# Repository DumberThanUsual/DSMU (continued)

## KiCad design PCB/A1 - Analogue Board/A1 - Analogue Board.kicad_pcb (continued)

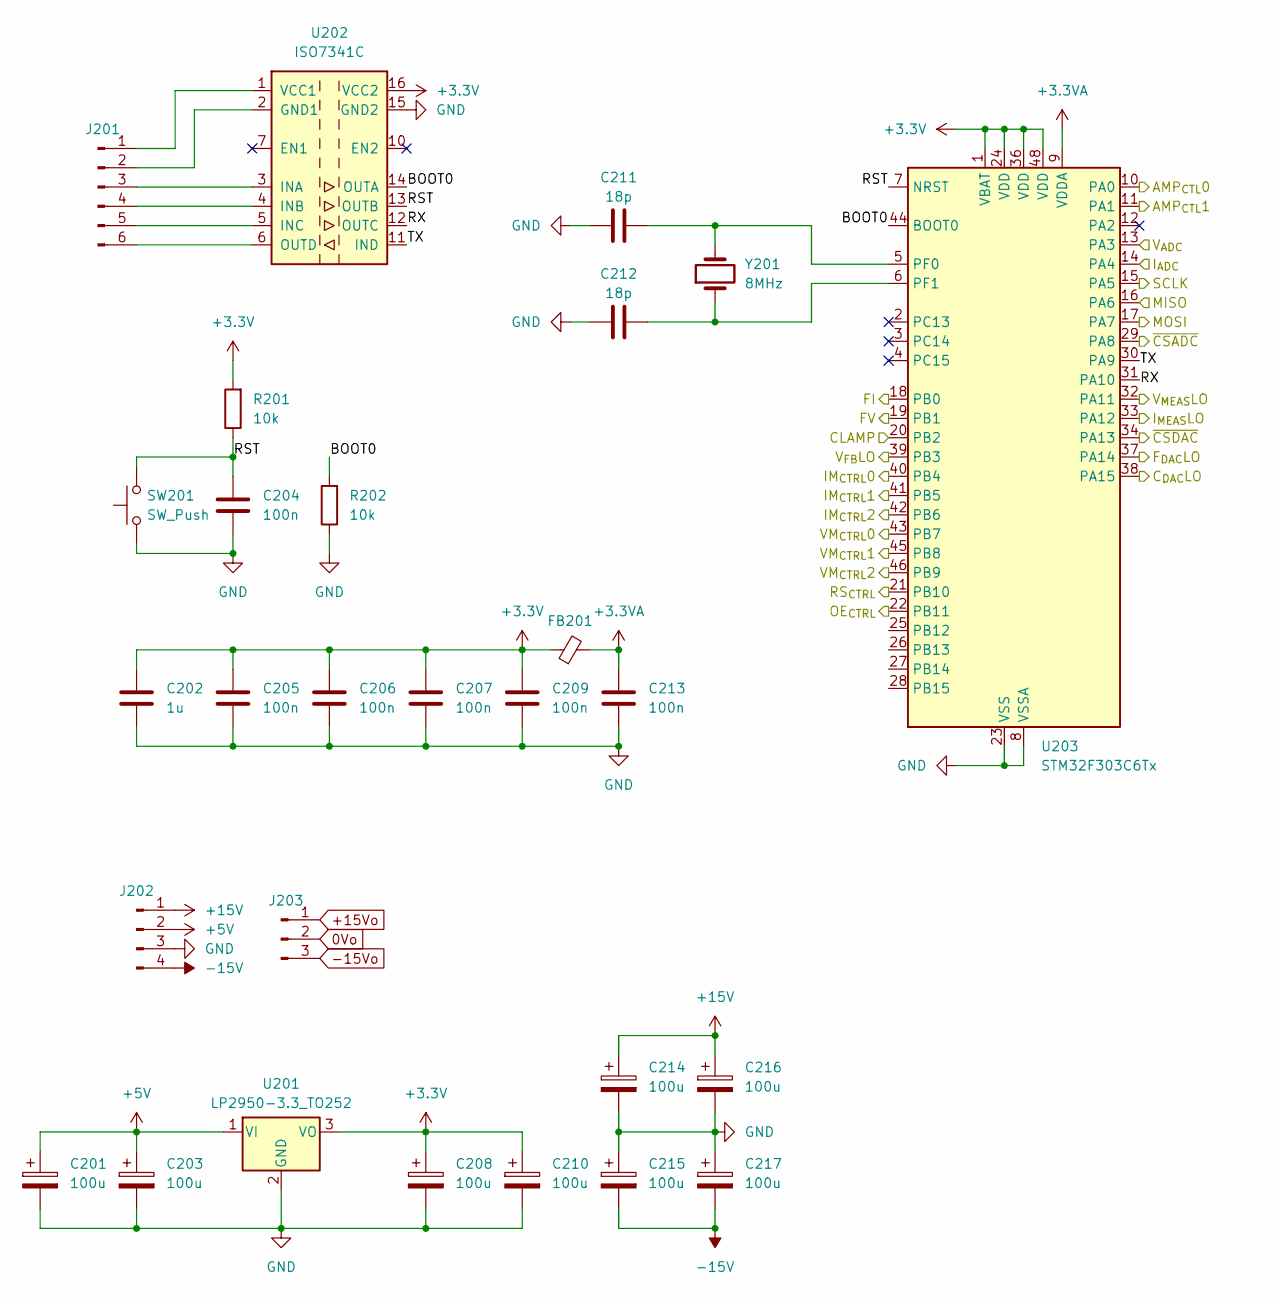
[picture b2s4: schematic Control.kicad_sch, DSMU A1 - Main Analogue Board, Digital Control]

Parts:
C201, C203, C208, C210, C214, C215, C216, C217: 100u; CP_Radial_D8.0mm_P3.50mm
C202: 1u; C_0603_1608Metric
C204, C205, C206, C207, C209, C213: 100n; C_0603_1608Metric
C211, C212: 18p; C_0603_1608Metric
FB201: FerriteBead_Small; L_0603_1608Metric
J201: Conn_01x06_Pin; PinHeader_1x06_P2.54mm_Vertical
J202: Conn_01x04_Pin; PinHeader_1x04_P2.54mm_Vertical
J203: Conn_01x03_Pin; PinHeader_1x03_P2.54mm_Vertical
R201, R202: 10k; R_0603_1608Metric
SW201: SW_Push; SW_SPST_Omron_B3FS-105xP
U201: LP2950-3.3_TO252; TO-252-3_TabPin2
U202: ISO7341C; SOIC-16W_7.5x10.3mm_P1.27mm
U203: STM32F303C6Tx; LQFP-48_7x7mm_P0.5mm
Y201: 8MHz; Crystal_HC18-U_Vertical

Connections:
0Vo: J203.2; also elsewhere on the board
+3.3V: C202.1, C205.1, C206.1, C207.1, C208.1, C209.1, C210.1, FB201.1, R201.2, U201.3 (VO), U202.16 (VCC2), U203.1 (VBAT), U203.24 (VDD), U203.36 (VDD), U203.48 (VDD); also elsewhere on the board
+3.3VA: C213.1, FB201.2, U203.9 (VDDA)
+5V: C201.1, C203.1, J202.2, U201.1 (VI); also elsewhere on the board
+15V: C214.1, C216.1, J202.1; also elsewhere on the board
+15Vo: J203.1; also elsewhere on the board
-15V: C215.2, C217.2, J202.4; also elsewhere on the board
-15Vo: J203.3; also elsewhere on the board
/Clamp: U203.20 (PB2); also elsewhere on the board
/Data Converters/C_{DAC}LO: U203.38 (PA15); also elsewhere on the board
/Data Converters/F_{DAC}LO: U203.37 (PA14); also elsewhere on the board
/Data Converters/I_{MEAS}LO: U203.33 (PA12); also elsewhere on the board
/Data Converters/MISO: U203.16 (PA6); also elsewhere on the board
/Data Converters/MOSI: U203.17 (PA7); also elsewhere on the board
/Data Converters/SCLK: U203.15 (PA5); also elsewhere on the board
/Data Converters/V_{MEAS}LO: U203.32 (PA11); also elsewhere on the board
/Data Converters/~CSADC: U203.29 (PA8); also elsewhere on the board
/Data Converters/~CSDAC: U203.34 (PA13); also elsewhere on the board
/Digital Control/AMP_{CTL}0: U203.10 (PA0); also elsewhere on the board
/Digital Control/AMP_{CTL}1: U203.11 (PA1); also elsewhere on the board
/Digital Control/BOOT0: R202.2, U202.14 (OUTA), U203.44 (BOOT0)
/Digital Control/I_{ADC}: U203.14 (PA4); also elsewhere on the board
/Digital Control/RST: C204.1, R201.1, SW201.2, U202.13 (OUTB), U203.7 (NRST)
/Digital Control/RX: U202.12 (OUTC), U203.31 (PA10)
/Digital Control/TX: U202.11 (IND), U203.30 (PA9)
/Digital Control/V_{ADC}: U203.13 (PA3); also elsewhere on the board
/FI: U203.18 (PB0); also elsewhere on the board
/FV: U203.19 (PB1); also elsewhere on the board
/IM_{CTRL}0: U203.40 (PB4); also elsewhere on the board
/IM_{CTRL}1: U203.41 (PB5); also elsewhere on the board
/IM_{CTRL}2: U203.42 (PB6); also elsewhere on the board
/OE_{CTRL}: U203.22 (PB11); also elsewhere on the board
/RS_{CTRL}: U203.21 (PB10); also elsewhere on the board
/VM_{CTRL}0: U203.43 (PB7); also elsewhere on the board
/VM_{CTRL}1: U203.45 (PB8); also elsewhere on the board
/VM_{CTRL}2: U203.46 (PB9); also elsewhere on the board
/V_{FB}LO: U203.39 (PB3); also elsewhere on the board
GND: C201.2, C202.2, C203.2, C204.2, C205.2, C206.2, C207.2, C208.2, C209.2, C210.2, C211.1, C212.1, C213.2, C214.2, C215.1, C216.2, C217.1, J202.3, R202.1, SW201.1, U201.2 (GND), U202.9 (GND2), U202.15 (GND2), U203.8 (VSSA), U203.23 (VSS), U203.35 (VSS), U203.47 (VSS); also elsewhere on the board
unnamed: J201.1, U202.1 (VCC1)
unnamed: J201.2, U202.2 (GND1), U202.8 (GND1)
unnamed: J201.3, U202.3 (INA)
unnamed: J201.4, U202.4 (INB)
unnamed: J201.5, U202.5 (INC)
unnamed: J201.6, U202.6 (OUTD)
unnamed: C211.2, U203.5 (PF0), Y201.2
unnamed: C212.2, U203.6 (PF1), Y201.1

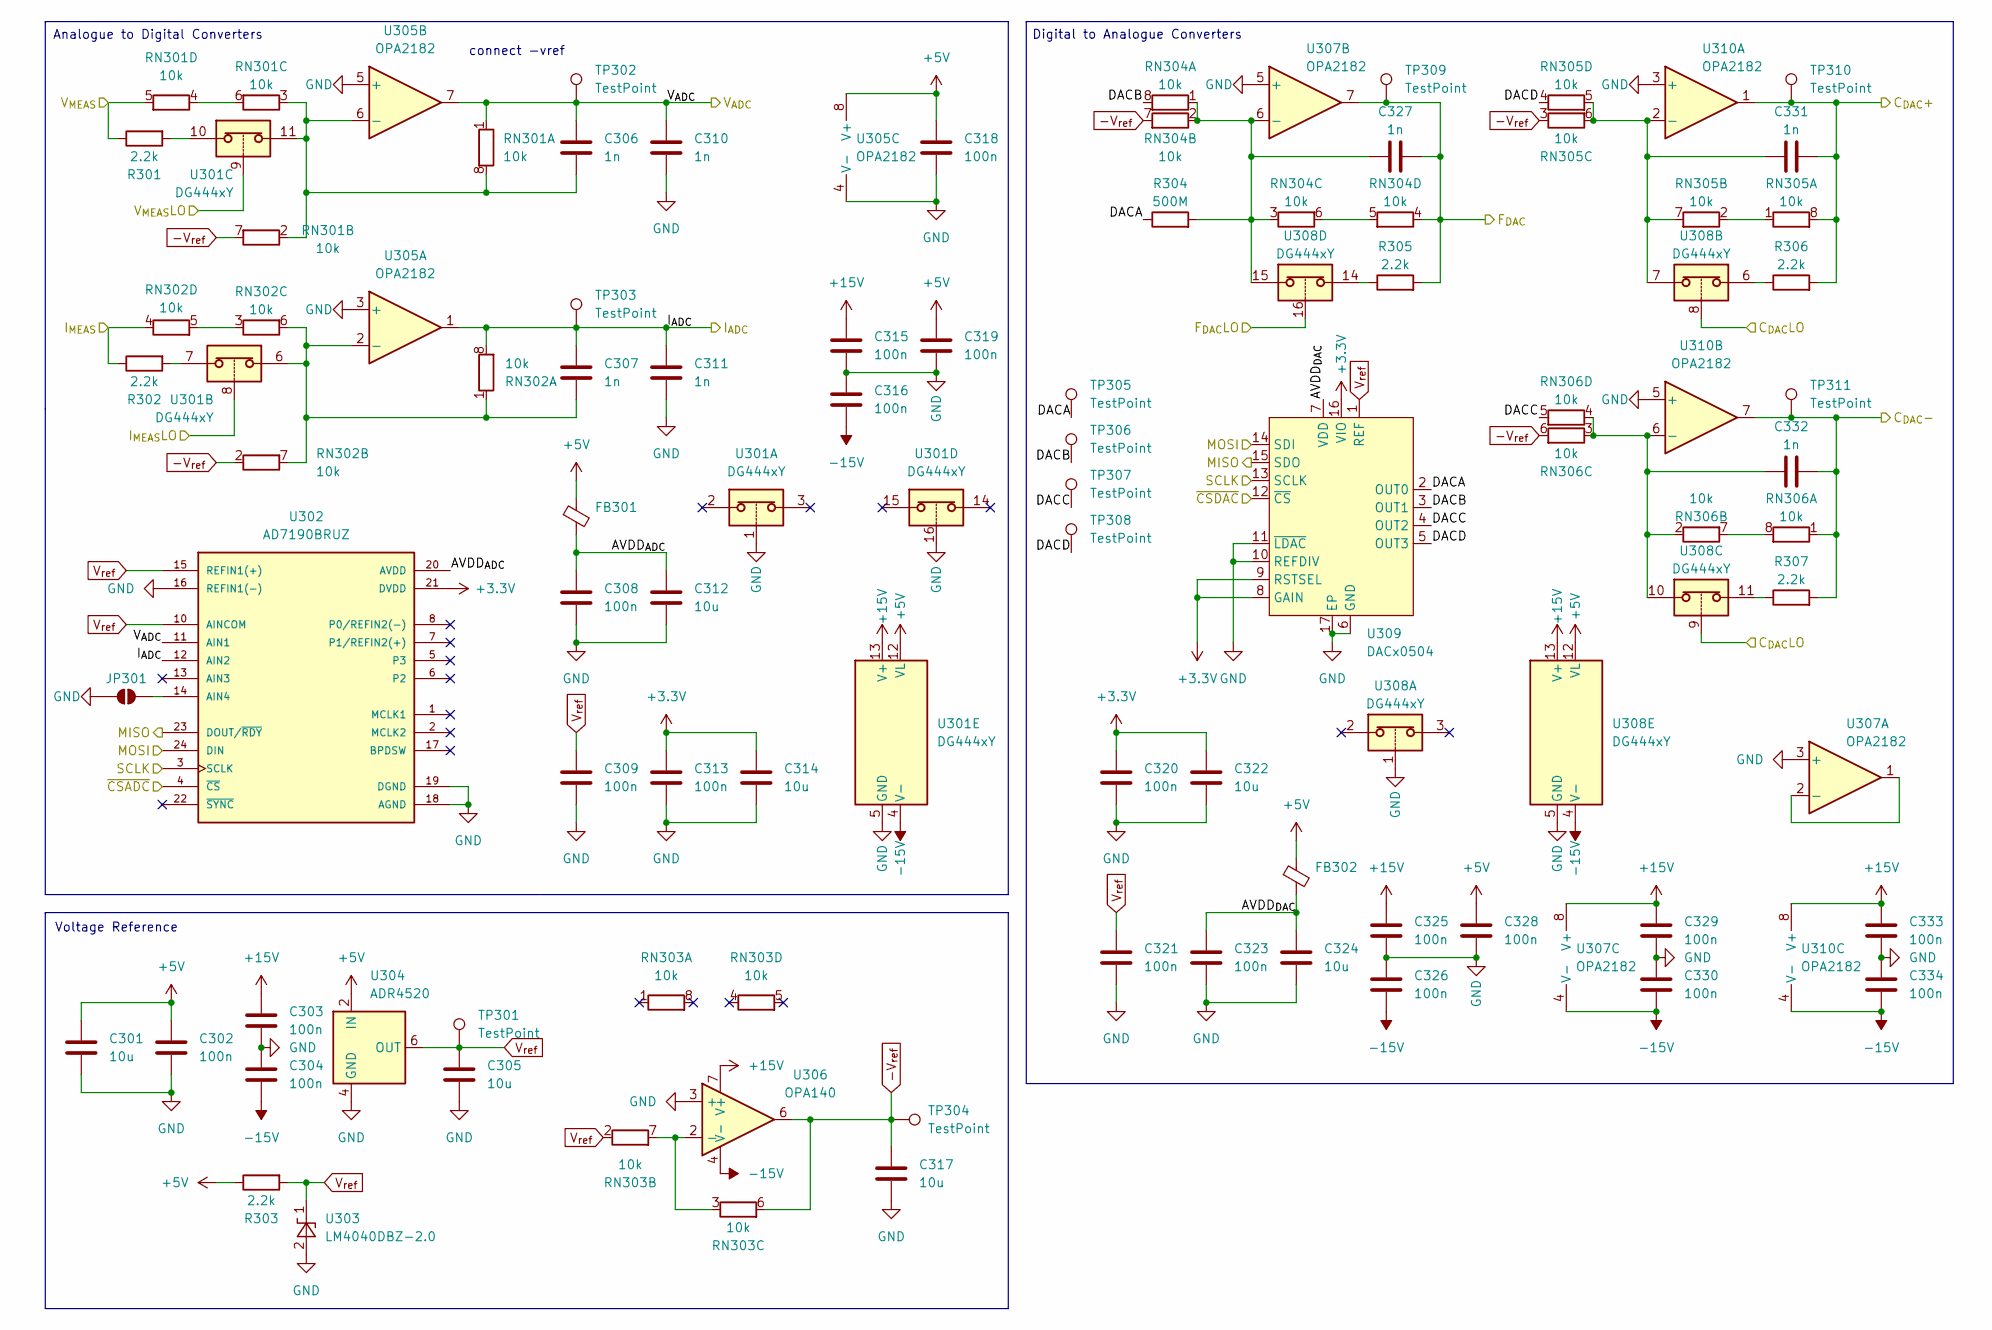
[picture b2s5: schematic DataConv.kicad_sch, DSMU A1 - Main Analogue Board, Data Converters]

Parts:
C301, C305, C312, C314, C317, C322, C324: 10u; C_0805_2012Metric
C302, C303, C304, C308, C309, C313, C315, C316, C318, C319, C320, C321, C323, C325, C326, C328, C329, C330, C333, C334: 100n; C_0603_1608Metric
C306, C307, C310, C311, C327, C331, C332: 1n; C_0603_1608Metric
FB301, FB302: FerriteBead_Small; L_0603_1608Metric
JP301: SolderJumper_2_Open; SolderJumper-2_P1.3mm_Open_RoundedPad1.0x1.5mm
R301, R302, R303, R305, R306, R307: 2.2k; R_0603_1608Metric
R304: 500M; R_1206_3216Metric
RN301, RN302, RN303, RN304, RN305, RN306: 10k; R_Array_Concave_4x0603
TP301, TP302, TP303, TP304, TP305, TP306, TP307, TP308, TP309, TP310, TP311: TestPoint; Pin_D1.0mm_L10.0mm
U301, U308: DG444xY; SOIC-16_3.9x9.9mm_P1.27mm
U302: AD7190BRUZ; SOP65P640X120-24N
U303: LM4040DBZ-2.0; SOT-23
U304: ADR4520; SOIC-8_3.9x4.9mm_P1.27mm
U305, U307, U310: OPA2182; SOIC-8_3.9x4.9mm_P1.27mm
U306: OPA140; SOIC-8_3.9x4.9mm_P1.27mm
U309: DACx0504; WQFN-16-1EP_3x3mm_P0.5mm_EP1.68x1.68mm_ThermalVias

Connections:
+3.3V: C313.1, C314.1, C320.1, C322.1, U302.21 (DVDD), U309.8 (GAIN), U309.9 (RSTSEL), U309.16 (VIO); also elsewhere on the board
+5V: C301.1, C302.1, C318.1, C319.1, C328.1, FB301.1, FB302.1, R303.1, U301.12 (VL), U304.2 (IN), U305.8 (V+), U308.12 (VL); also elsewhere on the board
+15V: C303.1, C315.1, C325.1, C329.1, C333.1, U301.13 (V+), U306.7 (V+), U307.8 (V+), U308.13 (V+), U310.8 (V+); also elsewhere on the board
-15V: C304.2, C316.2, C326.2, C330.2, C334.2, U301.4 (V-), U306.4 (V-), U307.4 (V-), U308.4 (V-), U310.4 (V-); also elsewhere on the board
-V_{ref}: C317.1, RN301.7 (R2.2), RN302.2 (R2.1), RN303.6 (R3.2), RN304.7 (R2.2), RN305.3 (R3.1), RN306.6 (R3.2), TP304.1, U306.6
/Crossover and Amplifier Control/C_{DAC}+: C331.2, R306.2, RN305.8 (R1.2), TP310.1, U310.1; also elsewhere on the board
/Crossover and Amplifier Control/C_{DAC}-: C332.2, R307.2, RN306.1 (R1.1), TP311.1, U310.7; also elsewhere on the board
/Crossover and Amplifier Control/F_{DAC}: C327.2, R305.2, RN304.4 (R4.1), TP309.1, U307.7; also elsewhere on the board
/Data Converters/AVDD_{ADC}: C308.1, C312.1, FB301.2, U302.20 (AVDD)
/Data Converters/AVDD_{DAC}: C323.1, C324.1, FB302.2, U309.7 (VDD)
/Data Converters/C_{DAC}LO: U308.8, U308.9; also elsewhere on the board
/Data Converters/DACA: R304.1, TP305.1, U309.2 (OUT0)
/Data Converters/DACB: RN304.8 (R1.2), TP306.1, U309.3 (OUT1)
/Data Converters/DACC: RN306.5 (R4.2), TP307.1, U309.4 (OUT2)
/Data Converters/DACD: RN305.4 (R4.1), TP308.1, U309.5 (OUT3)
/Data Converters/F_{DAC}LO: U308.16; also elsewhere on the board
/Data Converters/I_{ADC}: C307.1, C311.1, RN302.8 (R1.2), TP303.1, U302.12 (AIN2), U305.1; also elsewhere on the board
/Data Converters/I_{MEAS}LO: U301.8; also elsewhere on the board
/Data Converters/MISO: U302.23 (DOUT/~RDY), U309.15 (SDO); also elsewhere on the board
/Data Converters/MOSI: U302.24 (DIN), U309.14 (SDI); also elsewhere on the board
/Data Converters/SCLK: U302.3 (SCLK), U309.13 (SCLK); also elsewhere on the board
/Data Converters/V_{ADC}: C306.1, C310.1, RN301.1 (R1.1), TP302.1, U302.11 (AIN1), U305.7; also elsewhere on the board
/Data Converters/V_{MEAS}LO: U301.9; also elsewhere on the board
/Data Converters/~CSADC: U302.4 (~CS); also elsewhere on the board
/Data Converters/~CSDAC: U309.12 (~CS); also elsewhere on the board
/IM: R302.1, RN302.4 (R4.1); also elsewhere on the board
/VM: R301.1, RN301.5 (R4.2); also elsewhere on the board
GND: C301.2, C302.2, C303.2, C304.1, C305.2, C308.2, C309.2, C310.2, C311.2, C312.2, C313.2, C314.2, C315.2, C316.1, C317.2, C318.2, C319.2, C320.2, C321.2, C322.2, C323.2, C324.2, C325.2, C326.1, C328.2, C329.2, C330.1, C333.2, C334.1, JP301.2 (B), U301.1, U301.5 (GND), U301.16, U302.16 (REFIN1(-)), U302.18 (AGND), U302.19 (DGND), U303.2 (A), U304.4 (GND), U305.3 (+), U305.4 (V-), U305.5 (+), U306.3 (+), U307.3 (+), U307.5 (+), U308.1, U308.5 (GND), U309.6 (GND), U309.10 (REFDIV), U309.11 (~LDAC), U309.17 (EP), U310.3 (+), U310.5 (+); also elsewhere on the board
unnamed: JP301.1 (A), U302.14 (AIN4)
unnamed: R301.2, U301.10
unnamed: R302.2, U301.7
unnamed: R305.1, U308.14
unnamed: R306.1, U308.6
unnamed: R307.1, U308.11
unnamed: C306.2, RN301.2 (R2.1), RN301.3 (R3.1), RN301.8 (R1.2), U301.11, U305.6 (-)
unnamed: RN301.4 (R4.1), RN301.6 (R3.2)
unnamed: C307.2, RN302.1 (R1.1), RN302.6 (R3.2), RN302.7 (R2.2), U301.6, U305.2 (-)
unnamed: RN302.3 (R3.1), RN302.5 (R4.2)
unnamed: RN303.3 (R3.1), RN303.7 (R2.2), U306.2 (-)
unnamed: C327.1, R304.2, RN304.1 (R1.1), RN304.2 (R2.1), RN304.3 (R3.1), U307.6 (-), U308.15
unnamed: RN304.5 (R4.2), RN304.6 (R3.2)
unnamed: RN305.1 (R1.1), RN305.2 (R2.1)
unnamed: C331.1, RN305.5 (R4.2), RN305.6 (R3.2), RN305.7 (R2.2), U308.7, U310.2 (-)
unnamed: RN306.7 (R2.2), RN306.8 (R1.2)
unnamed: C332.1, RN306.2 (R2.1), RN306.3 (R3.1), RN306.4 (R4.1), U308.10, U310.6 (-)
unnamed: U307.1, U307.2 (-)
V_{ref}: C305.1, C309.1, C321.1, R303.2, RN303.2 (R2.1), TP301.1, U302.10 (AINCOM), U302.15 (REFIN1(+)), U303.1 (K), U304.6 (OUT), U309.1 (REF)

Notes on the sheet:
connect -vref
Voltage Reference
Digital to Analogue Converters
Analogue to Digital Converters

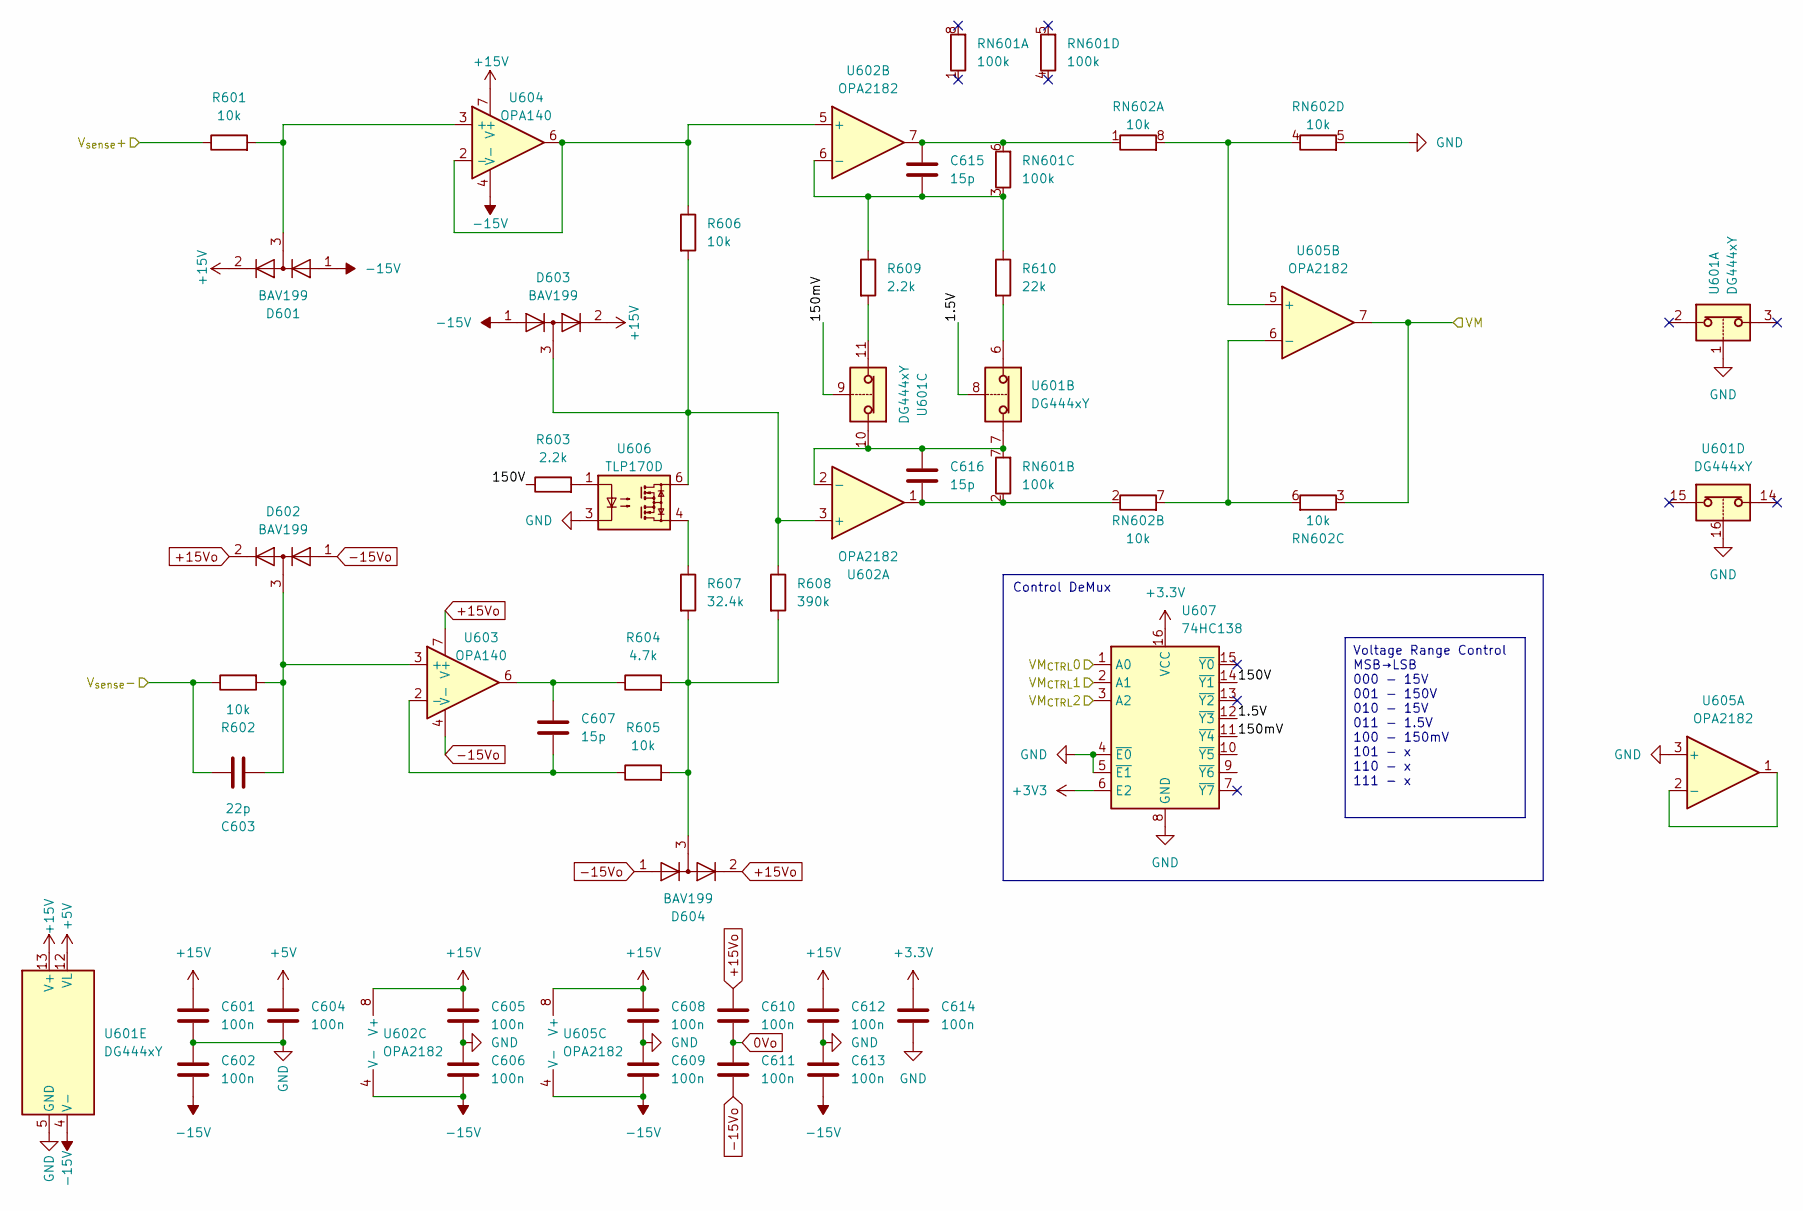
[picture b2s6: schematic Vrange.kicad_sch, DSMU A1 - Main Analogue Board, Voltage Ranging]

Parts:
C601, C602, C604, C605, C606, C608, C609, C610, C611, C612, C613, C614: 100n; C_0603_1608Metric
C603: 22p; C_0603_1608Metric
C607, C615, C616: 15p; C_0603_1608Metric
D601, D602, D603, D604: BAV199; SOT-23
R601, R602, R605, R606: 10k; R_0603_1608Metric
R603, R609: 2.2k; R_0603_1608Metric
R604: 4.7k; R_0603_1608Metric
R607: 32.4k; R_0805_2012Metric
R608: 390k; R_1206_3216Metric
R610: 22k; R_0603_1608Metric
RN601: 100k; R_Array_Concave_4x0603
RN602: 10k; R_Array_Concave_4x0603
U601: DG444xY; SOIC-16_3.9x9.9mm_P1.27mm
U602, U605: OPA2182; SOIC-8_3.9x4.9mm_P1.27mm
U603, U604: OPA140; SOIC-8_3.9x4.9mm_P1.27mm
U606: TLP170D; MFSOP6-4_4.4x3.6mm_P1.27mm
U607: 74HC138; SOIC-16_3.9x9.9mm_P1.27mm

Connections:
0Vo: C610.2, C611.1; also elsewhere on the board
+3.3V: C614.1, U607.16 (VCC); also elsewhere on the board
+3V3: U607.6 (E2); also elsewhere on the board
+5V: C604.1, U601.12 (VL); also elsewhere on the board
+15V: C601.1, C605.1, C608.1, C612.1, D601.2 (A), D603.2 (A), U601.13 (V+), U602.8 (V+), U604.7 (V+), U605.8 (V+); also elsewhere on the board
+15Vo: C610.1, D602.2 (A), D604.2 (A), U603.7 (V+); also elsewhere on the board
-15V: C602.2, C606.2, C609.2, C613.2, D601.1 (K), D603.1 (K), U601.4 (V-), U602.4 (V-), U604.4 (V-), U605.4 (V-); also elsewhere on the board
-15Vo: C611.2, D602.1 (K), D604.1 (K), U603.4 (V-); also elsewhere on the board
/VM: RN602.3 (R3.1), U605.7; also elsewhere on the board
/VM_{CTRL}0: U607.1 (A0); also elsewhere on the board
/VM_{CTRL}1: U607.2 (A1); also elsewhere on the board
/VM_{CTRL}2: U607.3 (A2); also elsewhere on the board
/Voltage Ranging/1.5V: U601.8, U607.12 (~Y3)
/Voltage Ranging/150V: R603.1, U607.14 (~Y1)
/Voltage Ranging/150mV: U601.9, U607.11 (~Y4)
/Voltage Ranging/V_{sense}+: R601.1; also elsewhere on the board
/Voltage Ranging/V_{sense}-: C603.1, R602.1; also elsewhere on the board
GND: C601.2, C602.1, C604.2, C605.2, C606.1, C608.2, C609.1, C612.2, C613.1, C614.2, RN602.5 (R4.2), U601.1, U601.5 (GND), U601.16, U605.3 (+), U606.3, U607.4 (~E0), U607.5 (~E1), U607.8 (GND); also elsewhere on the board
unnamed: C607.1, R604.1, U603.6
unnamed: D604.3 (K), R604.2, R605.2, R607.2, R608.2
unnamed: R603.2, U606.1
unnamed: R607.1, U606.4
unnamed: R609.2, U601.11
unnamed: R610.2, U601.6
unnamed: C616.2, RN601.2 (R2.1), RN602.2 (R2.1), U602.1
unnamed: C616.1, RN601.7 (R2.2), U601.7, U601.10, U602.2 (-)
unnamed: C615.2, R609.1, R610.1, RN601.3 (R3.1), U602.6 (-)
unnamed: C615.1, RN601.6 (R3.2), RN602.1 (R1.1), U602.7
unnamed: RN602.4 (R4.1), RN602.8 (R1.2), U605.5 (+)
unnamed: RN602.6 (R3.2), RN602.7 (R2.2), U605.6 (-)
unnamed: D603.3 (K), R606.2, R608.1, U602.3 (+), U606.6
unnamed: R606.1, U602.5 (+), U604.2 (-), U604.6
unnamed: C603.2, D602.3 (K), R602.2, U603.3 (+)
unnamed: C607.2, R605.1, U603.2 (-)
unnamed: D601.3 (K), R601.2, U604.3 (+)
unnamed: U605.1, U605.2 (-)

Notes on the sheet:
Voltage Range Control MSB→LSB 000 - 15V 001 - 150V 010 - 15V 011 - 1.5V 100 - 150mV 101 - x 110 - x 111 - x
Control DeMux

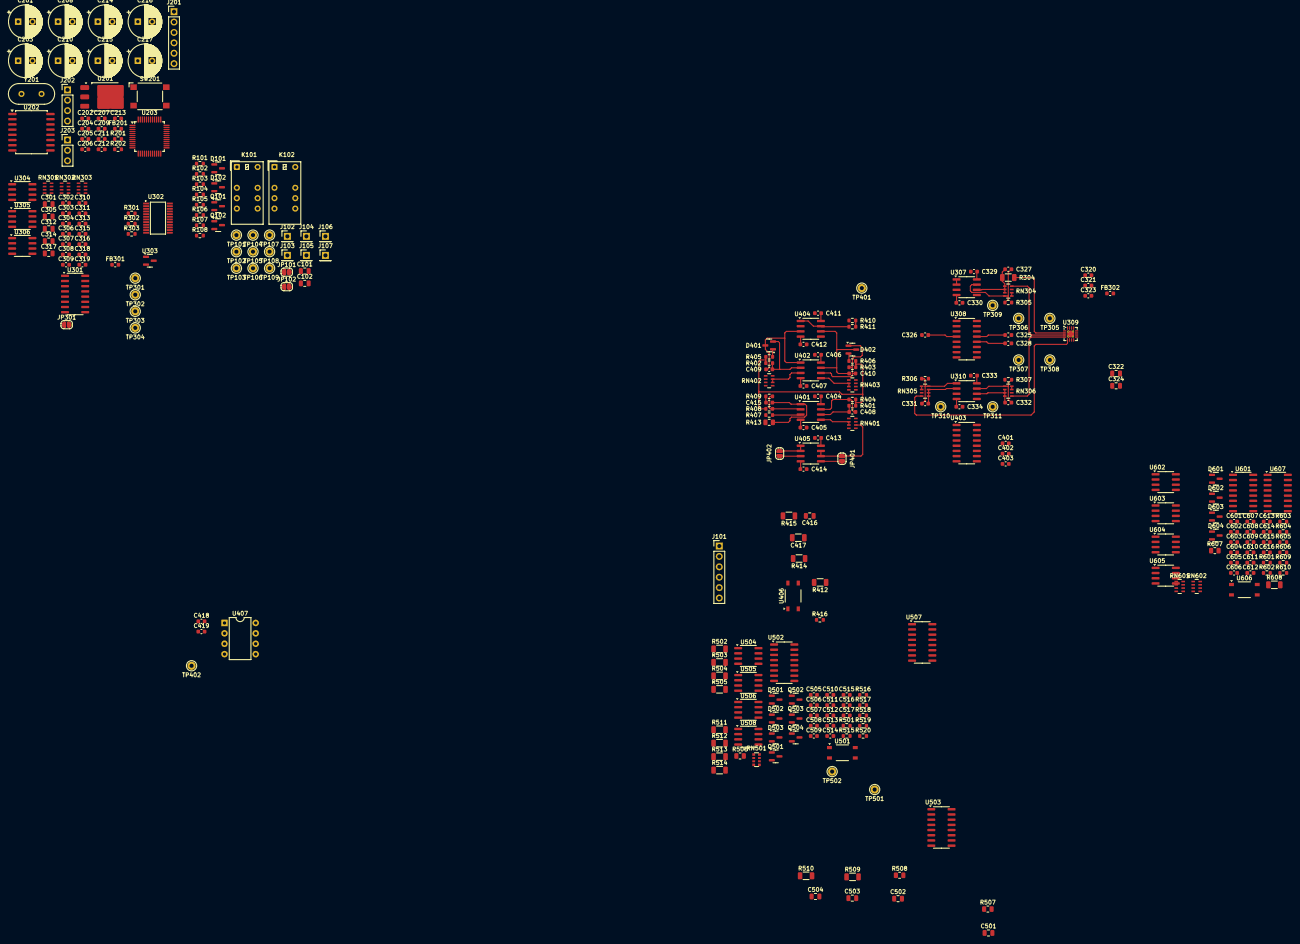
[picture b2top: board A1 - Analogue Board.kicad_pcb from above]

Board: 2 copper layers, 278 parts (0 on the bottom side), 174 nets.

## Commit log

2024-11-12 Add gitignore
